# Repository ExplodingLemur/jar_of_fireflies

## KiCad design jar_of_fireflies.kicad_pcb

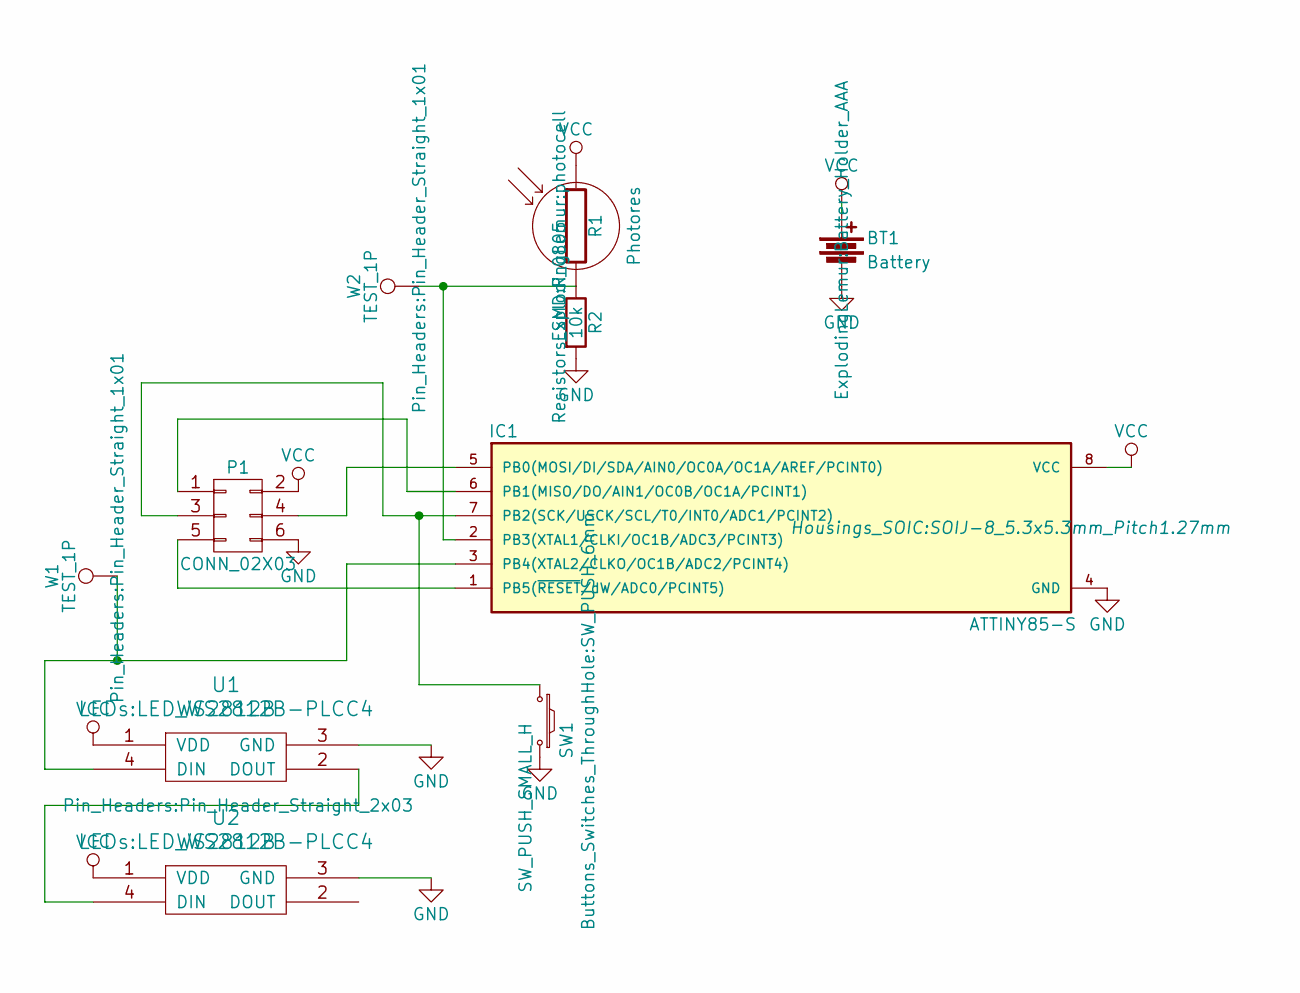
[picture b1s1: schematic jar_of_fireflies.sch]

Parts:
BT1: Battery; Battery_Holder_AAA
IC1: ATTINY85-S; SOIJ-8_5.3x5.3mm_Pitch1.27mm
P1: CONN_02X03; Pin_Header_Straight_2x03
R1: Photores; photocell
R2: 10k; R_0805
SW1: SW_PUSH_SMALL_H; SW_PUSH_6mm
U1, U2: WS2812B; LED_WS2812B-PLCC4
W1, W2: TEST_1P; Pin_Header_Straight_1x01

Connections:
GND: BT1.2, IC1.4 (GND), P1.6, R2.2, SW1.2, U1.3 (GND), U2.3 (GND)
unnamed: IC1.1 (PB5(~RESET~/dW/ADC0/PCINT5)), P1.5
unnamed: IC1.2 (PB3(XTAL1/CLKI/OC1B/ADC3/PCINT3)), R1.2, R2.1, W2.1
unnamed: IC1.3 (PB4(XTAL2/CLKO/OC1B/ADC2/PCINT4)), U1.4 (DIN), W1.1
unnamed: IC1.5 (PB0(MOSI/DI/SDA/AIN0/OC0A/OC1A/AREF/PCI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), P1.4
unnamed: IC1.6 (PB1(MISO/DO/AIN1/OC0B/OC1A/PCINT1)), P1.1
unnamed: IC1.7 (PB2(SCK/USCK/SCL/T0/INT0/ADC1/PCINT2)), P1.3, SW1.1
unnamed: U1.2 (DOUT), U2.4 (DIN)
VCC: BT1.1, IC1.8 (VCC), P1.2, R1.1, U1.1 (VDD), U2.1 (VDD)

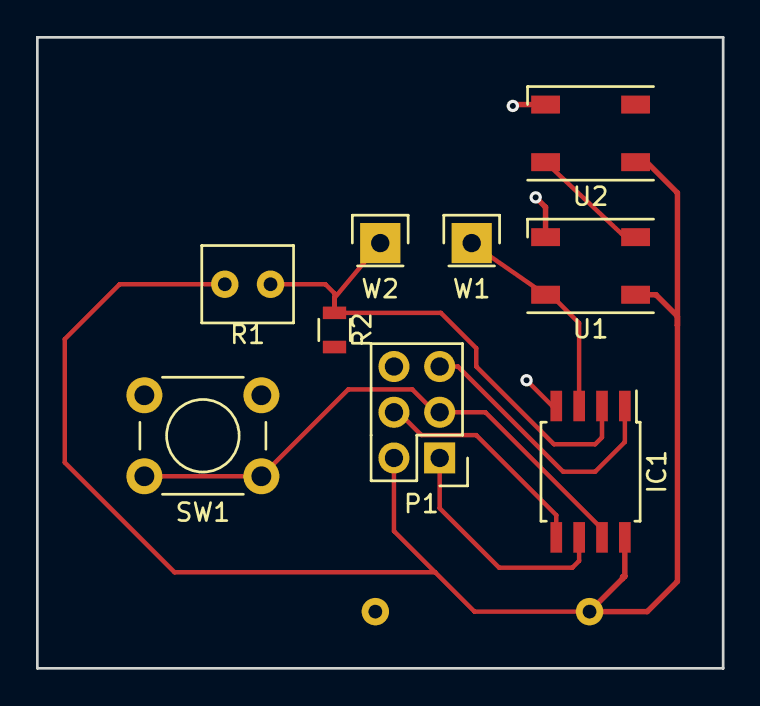
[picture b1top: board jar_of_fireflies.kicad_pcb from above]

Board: 2 copper layers, 38.1 x 35.1 mm, 10 parts (1 on the bottom side), 9 nets.

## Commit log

2016-10-02 First commit, with test boards for proof-of-concept/software dev
2016-10-02 Added bill of materials for test board

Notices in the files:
jar_of_fireflies.kicad_pcb:
CC-BY-SA
